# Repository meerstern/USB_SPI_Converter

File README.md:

# USB-SPI変換基板
USB SPI Converter with MCP2210
## 概要
  * USBをSPIマスタに変換する基板です
  * デバイスの動作確認やラピッドプロトタイピングに最適です
  * [MCP2210][1]を用いたUSB-SPI変換アダプタです
  * PMOD互換コネクタを搭載しており、SPIデバイスに簡単に接続可能です
  * VCC/信号電圧はスイッチ切替で5V/3.3V切替に対応しています  
    ※3.3V専用デバイスに5Vを加えないように注意してください
    
## 詳細
 *  MCP2210はHID標準デバイスとして認識されるため、ドライバは不要です
 *  MCP2210の仕様についてはデータシートを参照してください
 *  9つのGPIO及び1つのSPIポートが利用可能です
 *  SPIクロック速度は1.5k~ 12Mbpsまで対応しています
 *  全SPIモード(Mode 0, 1, 2, 3)に対応しています
 *  64byteの送受信バッファを搭載しています
 *  1回の送受信は最大65535byteまで対応しています
 *  HIDデバイスとして認識される仕様上、最大転送レートは64kByte/sec程度となります  
 *  COM-LEDはIO3に接続されています
 *  基板上のSPI Flashパターンを介して書き込む場合はIO0とIO2をhighに設定してください  
 *  USB5V電源入力側に350mA定格のリセッタブルヒューズを搭載しています  
 *  給電可能な電流は3.3Vラインで最大150mA前後、5Vラインで最大350mAです  

## サンプル例
 * MCP2210 Utility  
 [Microchip社MCP2210 Utility][2]からGUIでSPI通信をすることが可能です
 * Web USB SPI  
 Web USB HID APIを用いた[ツールでブラウザから操作するアプリ][3]です。オフラインでも動作可能です。
 * Web USB SPI Flash Tool  
 Web USB HID APIを用いた[ツールでブラウザからSPI Flashの読込/書込するアプリ][4]です。オフラインでも動作可能です。

## ピンアサイン

## 外観
 * 基板サイズ45mm x 25mm(突起部除く)
 * 固定穴M3x2、幅19mm 

## 販売サイト
  * [スイッチサイエンス][5]

[1]: https://www.microchip.com/en-us/product/MCP2210
[2]: https://ww1.microchip.com/downloads/en/DeviceDoc/MCP2210Utility-v1.2.3-windows-installer.zip
[3]: https://meerstern.github.io/web_usb_spi.html
[4]: https://meerstern.github.io/web_spi_flash_tool.html
[5]: https://ssci.to/9394

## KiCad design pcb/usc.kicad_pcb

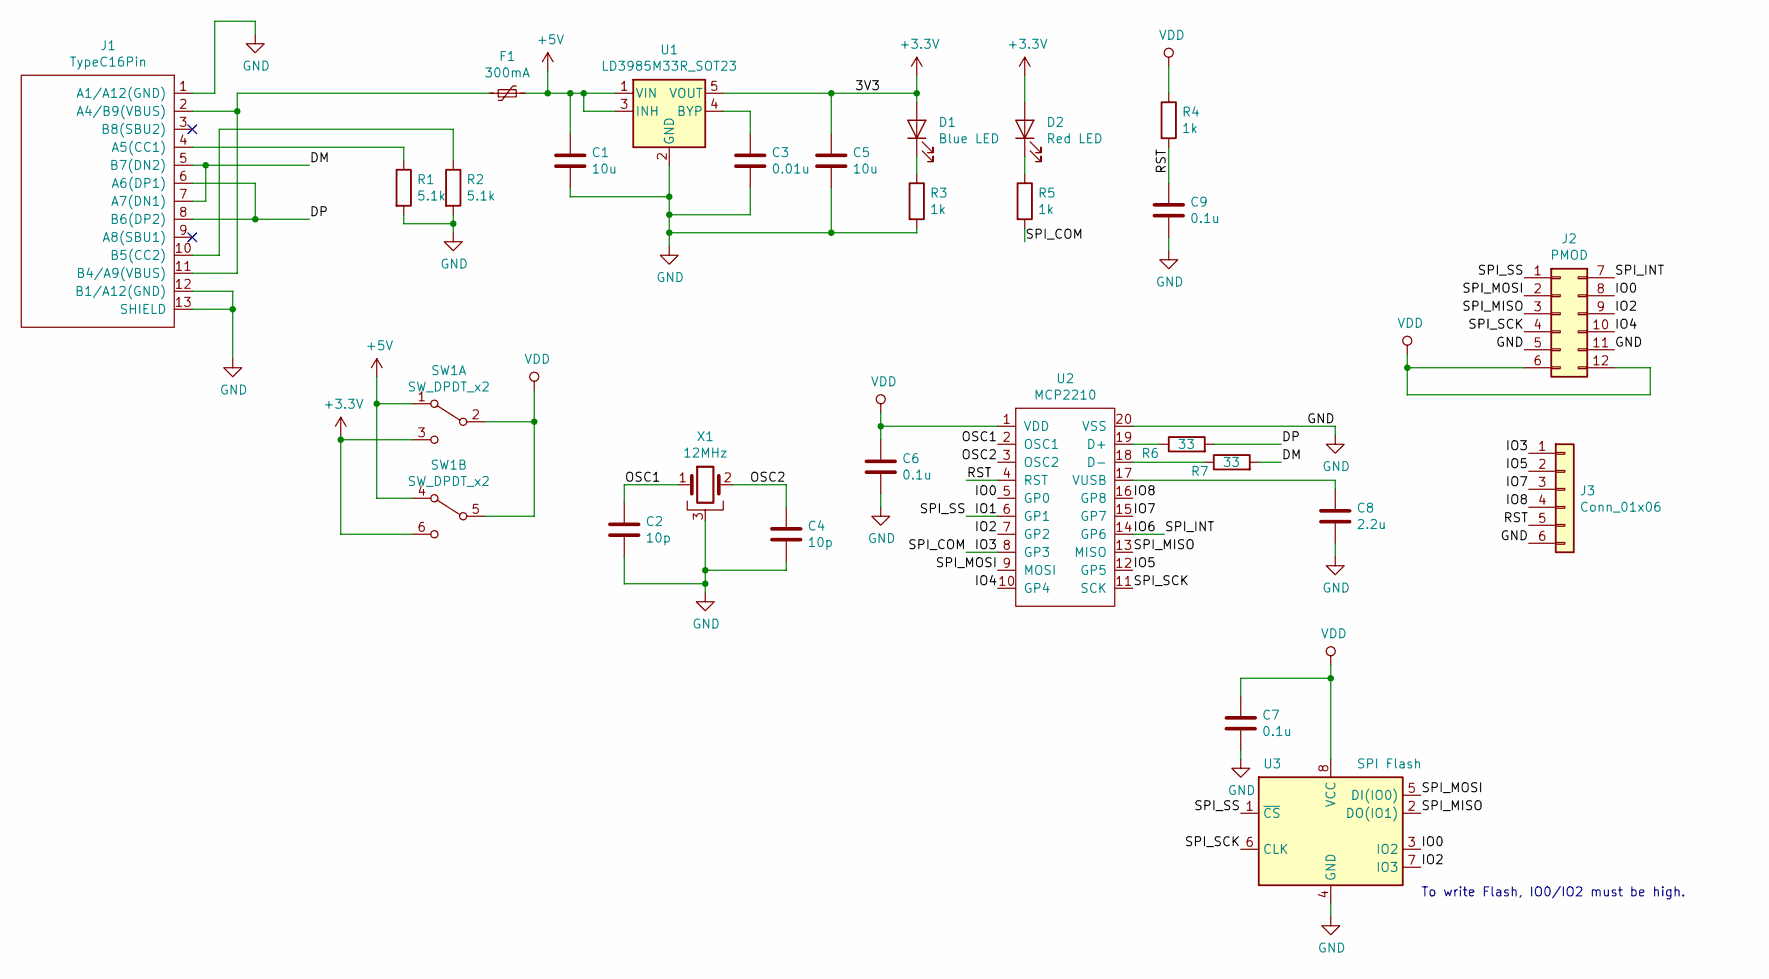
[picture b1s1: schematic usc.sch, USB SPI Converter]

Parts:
C1, C5: 10u; C_0805_2012Metric
C2, C4: 10p; C_0603_1608Metric
C3: 0.01u; C_0603_1608Metric
C6, C7, C9: 0.1u; C_0603_1608Metric
C8: 2.2u; C_0603_1608Metric
D1: Blue LED; D_0603_1608Metric
D2: Red LED; D_0603_1608Metric
F1: 300mA; Fuse_0603_1608Metric
J1: TypeC16Pin; TypeC_16Pin
J2: PMOD
J3: Conn_01x06; PinHeader_1x06_P2.54mm_Vertical
R1, R2: 5.1k; R_0603_1608Metric
R3, R4, R5: 1k; R_0603_1608Metric
R6, R7: 33; R_0603_1608Metric
SW1: SW_DPDT_x2; DPDT_SMD
U1: LD3985M33R_SOT23; SOT-23-5
U2: MCP2210; TSSOP-20_4.4x6.5mm_P0.65mm
U3: SPI Flash; DIP-8_W7.62mm
X1: 12MHz; FA238V

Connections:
+3V3: C5.1, D1.2 (A), D2.2 (A), SW1.3 (C), SW1.6 (C), U1.5 (VOUT)
+5V: C1.1, F1.2, SW1.1 (A), SW1.4 (A), U1.1 (VIN), U1.3 (INH)
/DM: J1.5 (B7(DN2)), J1.7 (A7(DN1)), R7.2
/DP: J1.6 (A6(DP1)), J1.8 (B6(DP2)), R6.2
/IO0: J2.8, U2.5 (GP0), U3.3 (IO2)
/IO1: J2.1, U2.6 (GP1), U3.1 (~CS)
/IO2: J2.9, U2.7 (GP2), U3.7 (IO3)
/IO3: J3.1, R5.2, U2.8 (GP3)
/IO4: J2.10, U2.10 (GP4)
/IO5: J3.2, U2.12 (GP5)
/IO6: J2.7, U2.14 (GP6)
/IO7: J3.3, U2.15 (GP7)
/IO8: J3.4, U2.16 (GP8)
/OSC1: C2.1, U2.2 (OSC1), X1.1
/OSC2: C4.1, U2.3 (OSC2), X1.2
/RST: C9.1, J3.5, R4.2, U2.4 (RST)
/SPI_MISO: J2.3, U2.13 (MISO), U3.2 (DO(IO1))
/SPI_MOSI: J2.2, U2.9 (MOSI), U3.5 (DI(IO0))
/SPI_SCK: J2.4, U2.11 (SCK), U3.6 (CLK)
GND: C1.2, C2.2, C3.2, C4.2, C5.2, C6.2, C7.2, C8.2, C9.2, J1.1 (A1/A12(GND)), J1.12 (B1/A12(GND)), J1.13 (SHIELD), J2.5, J2.11, J3.6, R1.2, R2.2, R3.2, U1.2 (GND), U2.20 (VSS), U3.4 (GND), X1.3
unnamed: C3.1, U1.4 (BYP)
unnamed: C8.1, U2.17 (VUSB)
unnamed: D1.1 (K), R3.1
unnamed: D2.1 (K), R5.1
unnamed: F1.1, J1.2 (A4/B9(VBUS)), J1.11 (B4/A9(VBUS))
unnamed: J1.4 (A5(CC1)), R1.1
unnamed: J1.10 (B5(CC2)), R2.1
unnamed: R6.1, U2.19 (D+)
unnamed: R7.1, U2.18 (D-)
VDD: C6.1, C7.1, J2.6, J2.12, R4.1, SW1.2 (B), SW1.5 (B), U2.1 (VDD), U3.8 (VCC)

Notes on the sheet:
To write Flash, IO0/IO2 must be high.

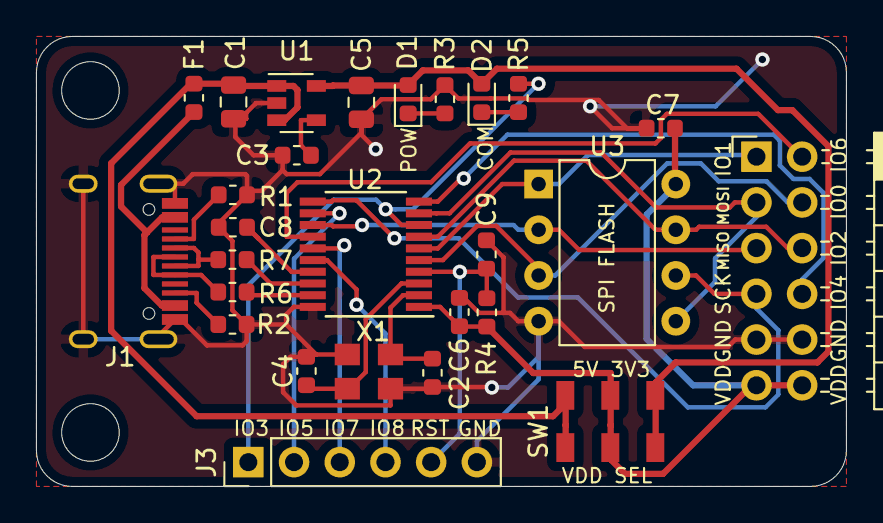
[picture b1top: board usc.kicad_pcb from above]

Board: 2 copper layers, 45.0 x 25.0 mm, 29 parts (0 on the bottom side), 30 nets.

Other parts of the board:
REF1, REF2: MountingHole_3.2mm_M3

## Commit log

2023-10-24 Add images
2023-11-19 Add PCB Files
